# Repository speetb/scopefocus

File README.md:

# Scopefocus

To reduce the amount of wires and additional modules on the telescope, this focuser controller is implemented on the back of a stepper motor and requires only 1 connection (USB)
At the same time, it will allow the use of more power and the connection to a temperature sensor and a RC servo (for future work).
The stepper driver is powered from either the USB or from an 5.5 mm barrel connector (up to 24 V) selectable by a jumper.

Currently works:
- Stepper motor control
- Reading temperature
- Communication with EKOS using Moonlite protocol https://indilib.org/media/kunena/attachments/1/HighResSteppermotor107.pdf
- IR command recieving (NEC protocol) and setting speed & position

Using hardware:
- Seeeduino XIAO https://wiki.seeedstudio.com/Seeeduino-XIAO/
- Fysetc TMC2130 v1.1 stepper motor driver https://wiki.fysetc.com/TMC2130
- TMP36 temperature sensor connected via a three-pin connector https://www.analog.com/media/en/technical-documentation/data-sheets/TMP35_36_37.pdf
- VS1838 IR reciever
- Nema 17 stepper motor

Using libraries:
- IRremote https://github.com/Arduino-IRremote/Arduino-IRremote
- Accelstepper https://www.airspayce.com/mikem/arduino/AccelStepper/index.html
- TMC2130 https://github.com/teemuatlut/TMC2130Stepper

TODO:
- ~~Implement faster IR recieve library. Maybe: https://github.com/NicoHood/IRLremote~~ Library only for AVR/ ESP boards
- Make temp reading fast (fast analog read) and non-blocking (example: BlinkWithOutDelay).
- Reduce/ eliminate floating point math.
- Create own fast stepper library using:
  - Direct port manipulation https://forum.seeedstudio.com/t/direct-port-access-in-arduino-ide/253807/6
  - 50 % duty cycle step pulsewidth as needed for TMC2130 mycroplyer https://download.mikroe.com/documents/datasheets/TMC220x_TMC222x_Datasheet.pdf#page=59
  - Microstepping to low value for fast moves and in the last phase of movement set the 'microstepping phase angle' using more micro-stepping.
- Eliminate backlash by always moving from one direction as the final move.
 
Not for now, but something to think about:
- Use the servo output and enable 'mirror lock' as a functionality (bool MirrorLock = true/ false) for Schmidt-Cassegrain telescopes.

Code originally adopted from https://github.com/orlyandico/arduino-focuser-moonlite

Here is the prototype connected to my 8" Celestron:

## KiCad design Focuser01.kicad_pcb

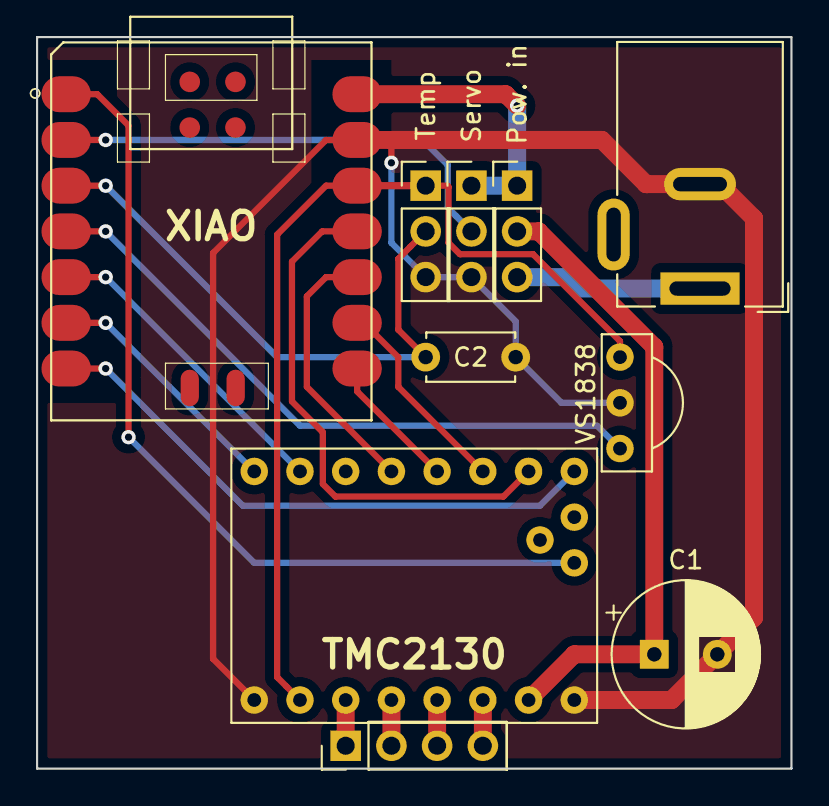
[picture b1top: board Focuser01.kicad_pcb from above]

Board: 2 copper layers, 41.9 x 40.6 mm, 10 parts (0 on the bottom side), 20 nets.

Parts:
C1: CP; CP_Radial_D8.0mm_P3.50mm
C2: C; C_Disc_D4.7mm_W2.5mm_P5.00mm
J1: Power in; BarrelJack_Wuerth_6941xx301002
J2: Motor; PinHeader_1x04_P2.54mm_Vertical
J3: Temp; PinHeader_1x03_P2.54mm_Vertical
J4: Servo; PinHeader_1x03_P2.54mm_Vertical
JP1: Pow. in; PinHeader_1x03_P2.54mm_Vertical
U1: XIAO; Seeeduino_XIAO
U2: TMC2130; tmc2130
U3: VS1838

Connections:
+3V3: J3.1, U1.12, U2.7, U3.3
+5V: J4.1, JP1.1, U1.14
+12V: J1.1, JP1.3
GND: C1.2, C2.2, J1.2, J3.3, J4.3, U1.13, U2.1, U2.8, U3.2
unnamed: C2.1, J3.2, U1.3
unnamed: J2.1, U2.6
unnamed: J2.2, U2.5
unnamed: J2.3, U2.4
unnamed: J2.4, U2.3
unnamed: J4.2, U1.2
unnamed: U1.1, U2.19
unnamed: U1.4, U3.1
unnamed: U1.5, U2.10
unnamed: U1.6, U2.9
unnamed: U1.7, U2.16
unnamed: U1.8, U2.13
unnamed: U1.9, U2.14
unnamed: U1.10, U2.12
unnamed: U1.11, U2.15
VBUS: C1.1, JP1.2, U2.2
